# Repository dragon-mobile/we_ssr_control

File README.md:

# we_ssr_control

<br/>

<br/>

The WEMOS Solid State Relay Controller is primarily meant to be
used with an open hardware solid state relay PCBs that is being co-developed
alongside this project as part of my Dragon Mobile GitHub organization to make
useful hardware with associated firmware and software for the tiny home, van
life and maker communities.

## Visual 3D examples

Top view<br/>
<br/>
Bottom view<br/>
<br/>

## Contributing

Contributors are welcome.
Please note that this project has a [Contributor Covenant Code of Conduct].
By participating in this project you agree to abide by its terms.

All intentionally contributed hardware will be considered to be contributed
under the [CERN] license without any additional terms or conditions.

All intentionally contributed code will be considered to be contributed
under a [MIT] license without any additional terms or conditions.
Please include your information in a comment on all code files for the copyright
etc.

All intentionally contributed documentation, CAD files and libraries, footprints,
artwork or non-code text like this README etc. will be considered to be
contributed under the same [CC-BY-SA] license without any additional terms or
conditions.

Pull requests are always welcome. For major changes, please open an issue first
to discuss what you would like to change.
Please make sure to update or add tests as appropriate for all software changes.

## Licenses

<br/>

All hardware is licensed under the

  * [CERN] - CERN-OHL-W-2.0
  
You can find a copy of the CERN Open Hardware License - Weakly-reciprocal v2.0
in the [LICENSE-CERN-OHL-W-2] file and the how-to guide in the
[CERN-HOWTO_GUIDE] file.

All code is licensed under the

  * [MIT] - MIT License

You can find a copy of the license in the [LICENSE-MIT] file.

All documentation like this README is licensed under the Creative Commons
Attribution-ShareAlike 4.0 International License (CC-BY-SA).

All original CAD files and libraries, footprints, and artwork are also licensed
under the
Creative Commons Attribution-ShareAlike 4.0 International License (CC-BY-SA).
You can find a copy of the [CC-BY-SA] license in the [LICENSE-CC-BY-SA] file.

If after reading the above license files, how-tos, and related FAQs on the
linked license sites on how they apply to the project please either open an
issue or contact me (Michael Cummings) via my Github email and I will try
to guided you through my understanding of how it works.

[CC-BY-SA]: http://creativecommons.org/licenses/by-sa/4.0/
[CERN]: https://ohwr.org/project/cernohl/wikis/Documents/CERN-OHL-version-2
[CERN-HOWTO_GUIDE]: docs/cern_ohl_w_v2_howto.pdf
[Contributor Covenant Code of Conduct]: CODE_OF_CONDUCT.md 
[LICENSE-CC-BY-SA]: LICENSE-CC-BY-SA
[LICENSE-CERN-OHL-W-2]: CERN-OHL-W-2
[LICENSE-MIT]: LICENSE-MIT
[MIT]: https://opensource.org/licenses/MIT

<hr>
Copyright &copy; 2022-2023, Michael Cummings<br/>

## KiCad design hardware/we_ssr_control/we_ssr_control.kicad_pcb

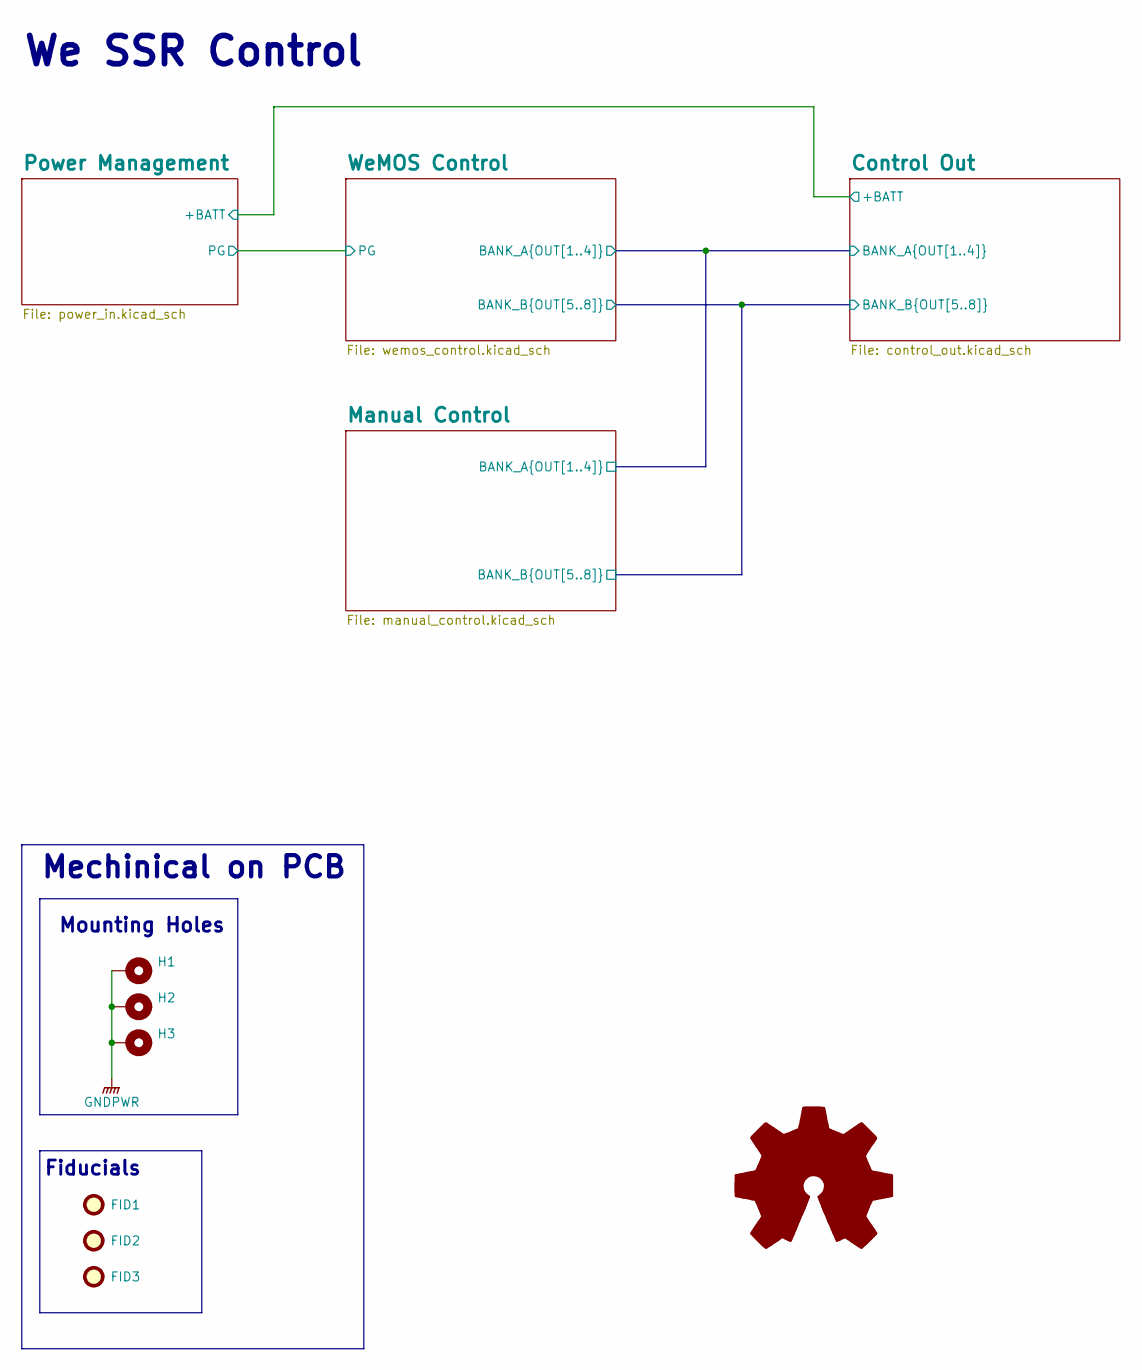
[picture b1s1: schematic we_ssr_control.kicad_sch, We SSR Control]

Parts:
FID1, FID2, FID3: Fiducial; Fiducial_0.5mm_Mask1mm
H1, H2, H3: MountingHole_Pad; MountingHole_3.2mm_M3_Pad_Via

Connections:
GNDPWR: H1.1, H2.1, H3.1; also elsewhere on the board

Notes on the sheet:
Fiducials
We SSR Control
Mechinical on PCB
Mounting Holes

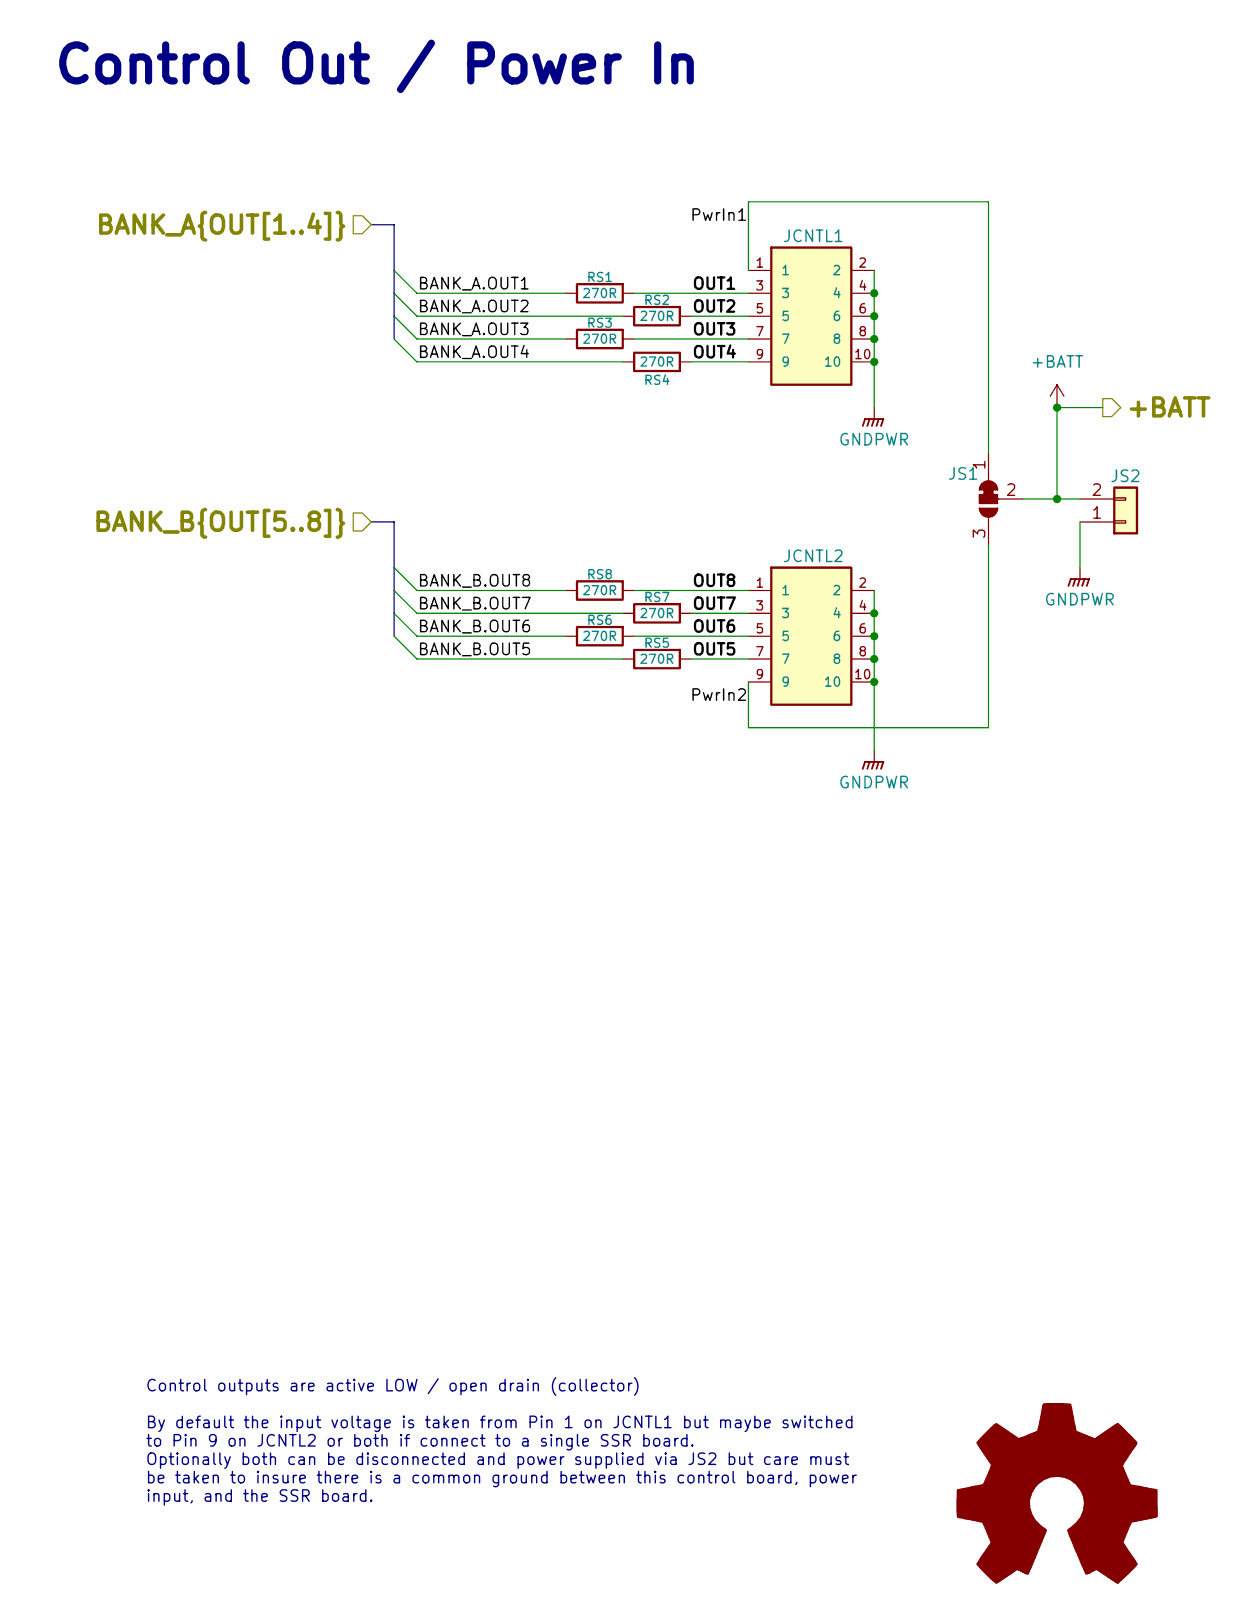
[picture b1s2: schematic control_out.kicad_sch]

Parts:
JCNTL1, JCNTL2: SHF-105-01-L-D-RA; SAMTEC_SHF-105-01-L-D-RA; Mouser Part Number 200-SHF10501LDRATR
JS1: SolderJumper_3_Bridged12; SolderJumper-3_P1.3mm_Bridged12_RoundedPad1.0x1.5mm_NumberL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
JS2: Conn_01x02; PinHeader_1x02_P1.00mm_Vertical
RS1, RS2, RS3, RS4, RS5, RS6, RS7, RS8: 270R; R_0603_1608Metric; Mouser Part Number 755-SDR03EZPJ271

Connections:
+BATT: JS1.2 (C), JS2.2; also elsewhere on the board
/Control Out/BANK_A.OUT1: RS1.1; also elsewhere on the board
/Control Out/BANK_A.OUT2: RS2.1; also elsewhere on the board
/Control Out/BANK_A.OUT3: RS3.1; also elsewhere on the board
/Control Out/BANK_A.OUT4: RS4.1; also elsewhere on the board
/Control Out/BANK_B.OUT5: RS5.1; also elsewhere on the board
/Control Out/BANK_B.OUT6: RS6.1; also elsewhere on the board
/Control Out/BANK_B.OUT7: RS7.1; also elsewhere on the board
/Control Out/BANK_B.OUT8: RS8.1; also elsewhere on the board
/Control Out/OUT1: JCNTL1.3, RS1.2
/Control Out/OUT2: JCNTL1.5, RS2.2
/Control Out/OUT3: JCNTL1.7, RS3.2
/Control Out/OUT4: JCNTL1.9, RS4.2
/Control Out/OUT5: JCNTL2.7, RS5.2
/Control Out/OUT6: JCNTL2.5, RS6.2
/Control Out/OUT7: JCNTL2.3, RS7.2
/Control Out/OUT8: JCNTL2.1, RS8.2
/Control Out/PwrIn1: JCNTL1.1, JS1.1 (A)
/Control Out/PwrIn2: JCNTL2.9, JS1.3 (B)
GNDPWR: JCNTL1.2, JCNTL1.4, JCNTL1.6, JCNTL1.8, JCNTL1.10, JCNTL2.2, JCNTL2.4, JCNTL2.6, JCNTL2.8, JCNTL2.10, JS2.1; also elsewhere on the board

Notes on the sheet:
Control Out / Power In
Control outputs are active LOW / open drain (collector) By default the input voltage is taken from Pin 1 on JCNTL1 but maybe switched to Pin 9 on JCNTL2 or both if connect to a single SSR board. Optionally both can be disconnected and power supplied via JS2 but care must be taken to insure there is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

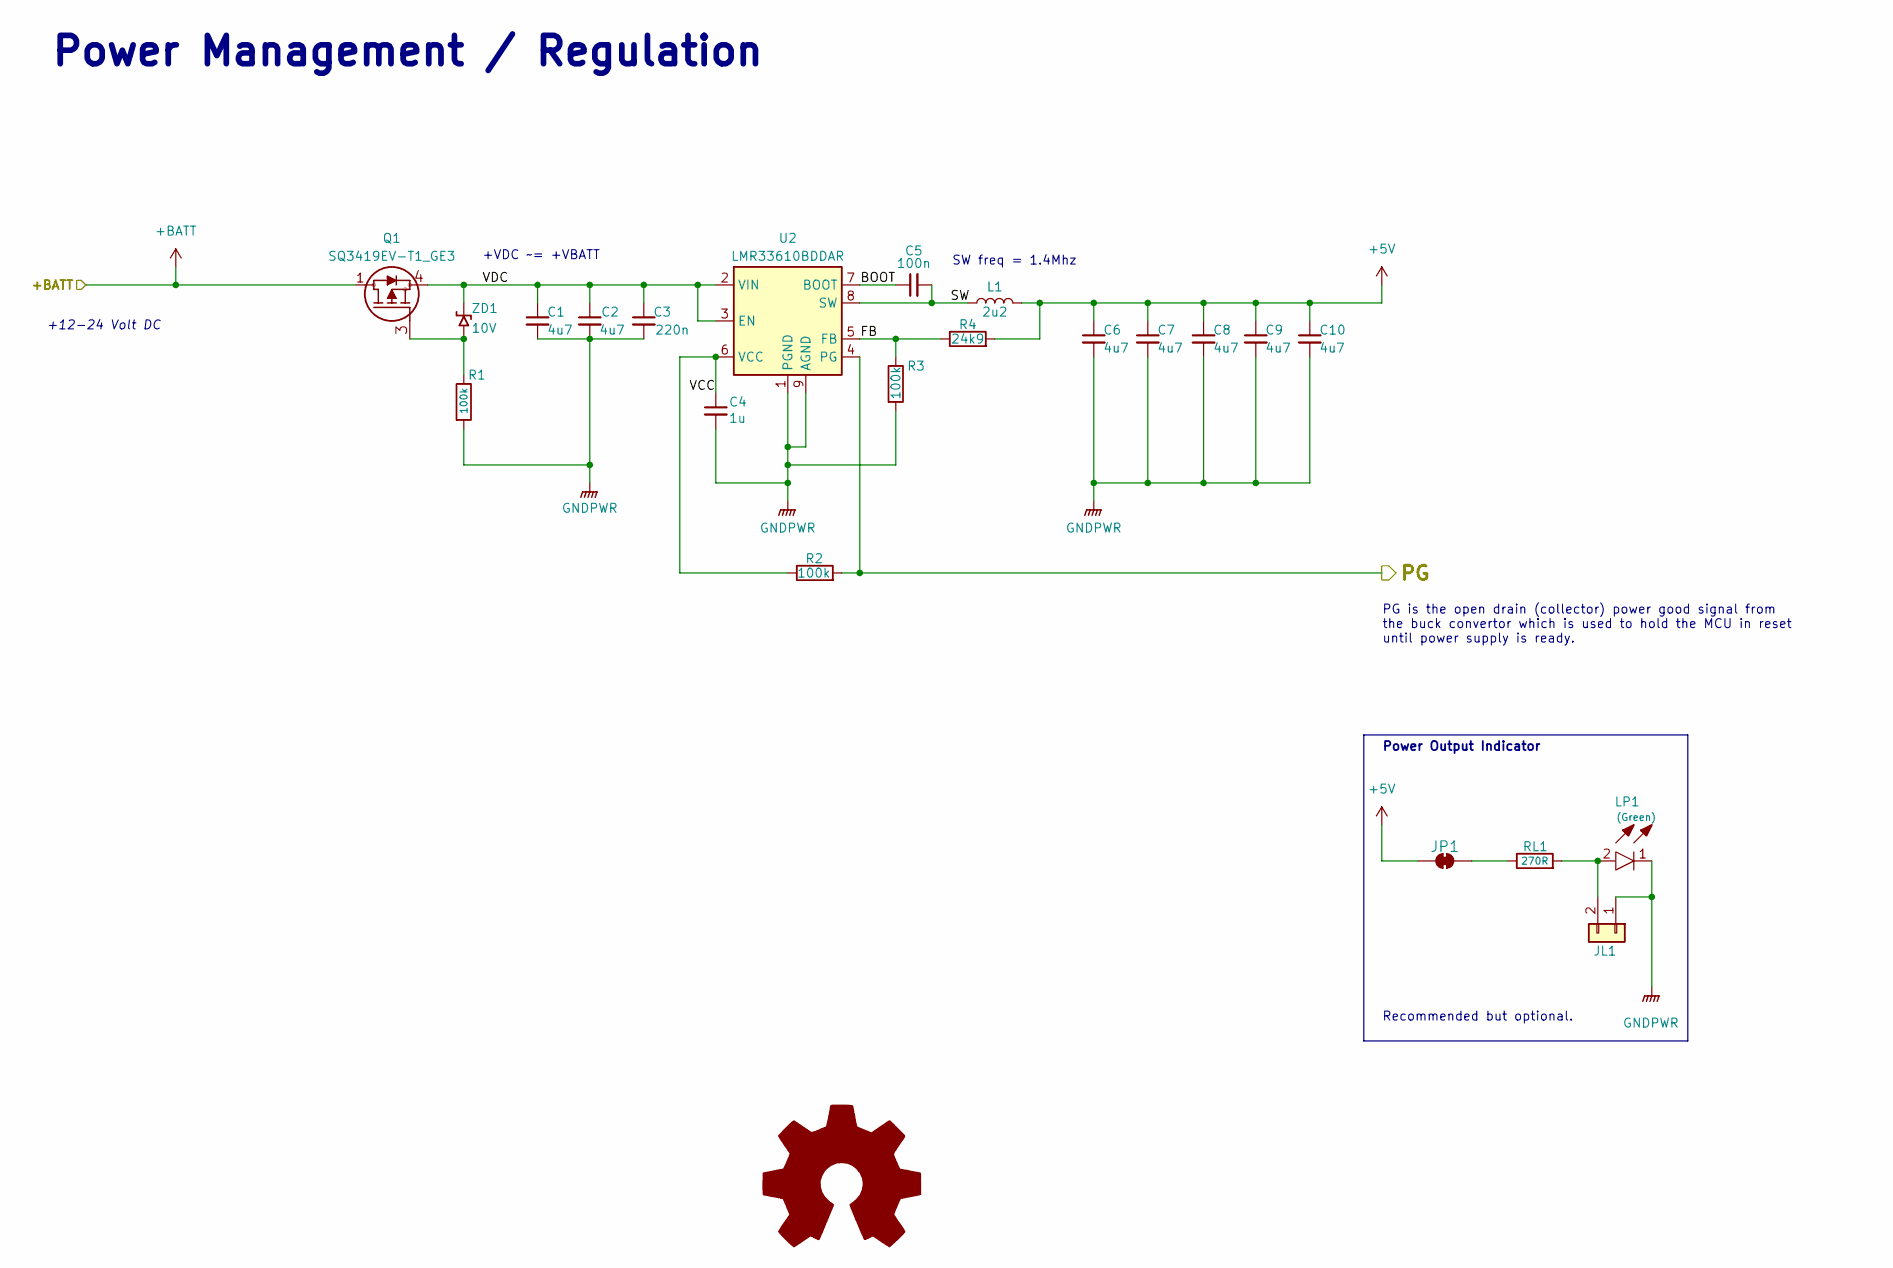
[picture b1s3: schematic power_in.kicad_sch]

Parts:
C1, C2, C6, C7, C8, C9, C10: 4u7; C_0805_2012Metric; Mouser Part Number 810-CGA4J1X7R1H475K1
C3: 220n; C_0603_1608Metric; Mouser Part Number 810-CGA3E3X7R1H224K
C4: 1u; C_0603_1608Metric; Mouser Part Number 810-CGA3E3X5R1H105K
C5: 100n; C_0603_1608Metric; Mouser Part Number 810-CGA3E2X7R1H104K
JL1: Conn_01x02; PinHeader_1x02_P1.00mm_Vertical
JP1: SolderJumper_2_Bridged; SolderJumper-2_P1.3mm_Bridged_RoundedPad1.0x1.5mm
L1: 2u2; L_1008_2520Metric; Mouser Part Number 810-TFM252012ALVA2R2
LP1: LTST-C190KGKT; LEDC1608X80N; Mouser Part Number 859-LTST-C190KGKT
Q1: SQ3419EV-T1_GE3; SOT95P284X110-6N; Mouser Part Number 78-SQ3419EV-T1_GE3
R1, R2, R3: 100k; R_0603_1608Metric; Mouser Part Number 667-ERJ-PA3F1003V
R4: 24k9; R_0603_1608Metric; Mouser Part Number 667-ERJ-PA3F2492V
RL1: 270R; R_0603_1608Metric; Mouser Part Number 755-SDR03EZPJ271
U2: LMR33610BDDAR; Texas_HSOP-8-1EP_3.9x4.9mm_P1.27mm_ThermalVias; Mouser Part Number 595-LMR33610BDDAR
ZD1: 10V; D_0805_2012Metric; Mouser Part Number 821-BZY55B10RBG

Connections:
+5V: C6.1, C7.1, C8.1, C9.1, C10.1, JP1.1 (A), L1.2, R4.2; also elsewhere on the board
+BATT: Q1.1 (D), Q1.2 (D), Q1.5 (D), Q1.6 (D); also elsewhere on the board
/Power Management/BOOT: C5.1, U2.7 (BOOT)
/Power Management/FB: R3.1, R4.1, U2.5 (FB)
/Power Management/PG: R2.2, U2.4 (PG); also elsewhere on the board
/Power Management/SW: C5.2, L1.1, U2.8 (SW)
/Power Management/VCC: C4.1, R2.1, U2.6 (VCC)
/Power Management/VDC: C1.1, C2.1, C3.1, Q1.4 (S), U2.2 (VIN), U2.3 (EN), ZD1.1
GNDPWR: C1.2, C2.2, C3.2, C4.2, C6.2, C7.2, C8.2, C9.2, C10.2, JL1.1, LP1.1, R1.2, R3.2, U2.1 (PGND), U2.9 (AGND); also elsewhere on the board
unnamed: JL1.2, LP1.2, RL1.2
unnamed: JP1.2 (B), RL1.1
unnamed: Q1.3 (G), R1.1, ZD1.2

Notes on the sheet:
+12-24 Volt DC
PG is the open drain (collector) power good signal from the buck convertor which is used to hold the MCU in reset until power supply is ready.
Recommended but optional.
SW freq = 1.4Mhz
Power Management / Regulation
Power Output Indicator
+VDC ~= +VBATT

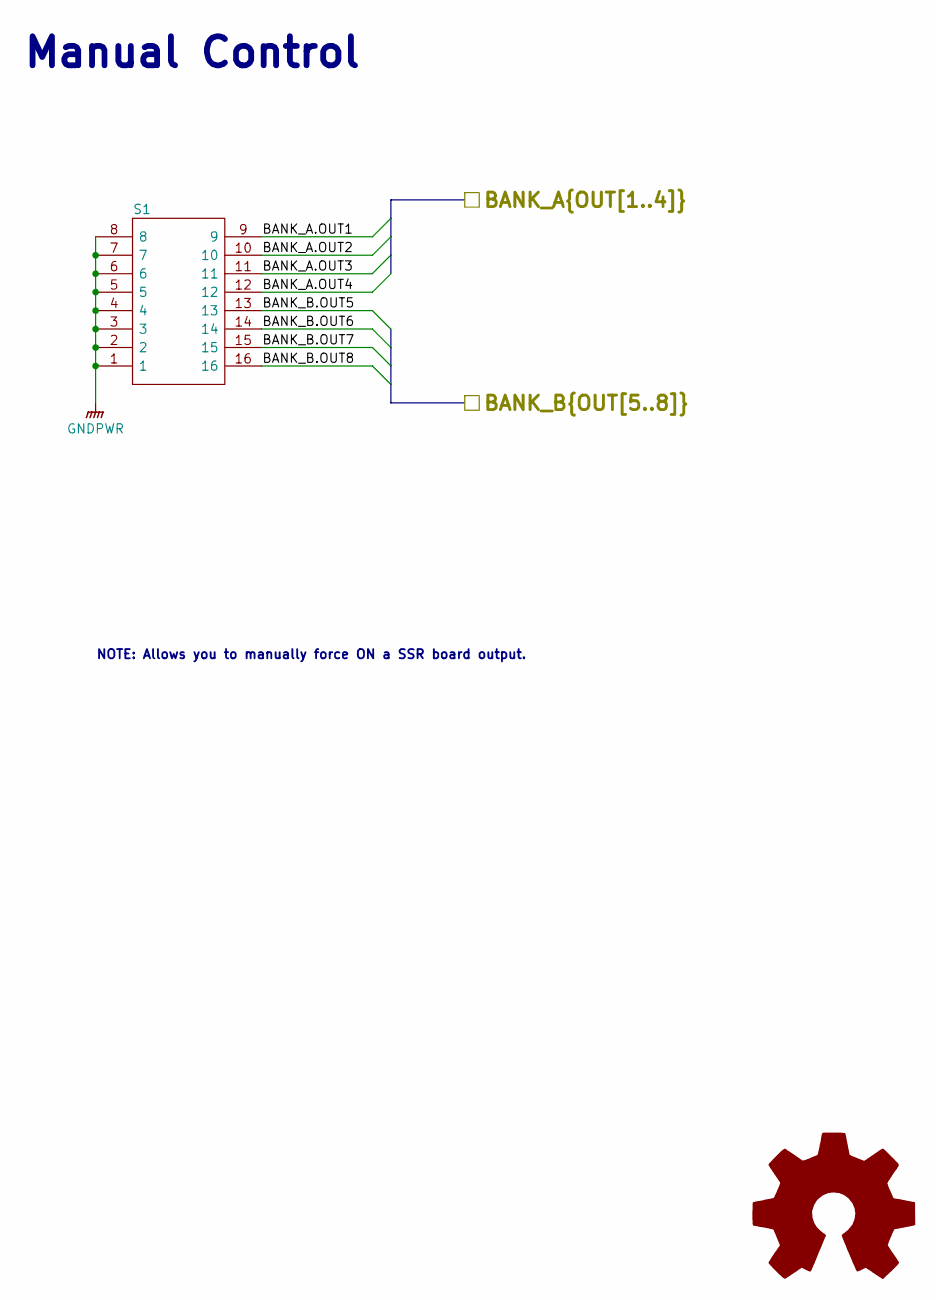
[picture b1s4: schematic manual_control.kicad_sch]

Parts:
S1: 193-8MS; 1938MS; Mouser Part Number 774-1938MS

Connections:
/Control Out/BANK_A.OUT1: S1.9; also elsewhere on the board
/Control Out/BANK_A.OUT2: S1.10; also elsewhere on the board
/Control Out/BANK_A.OUT3: S1.11; also elsewhere on the board
/Control Out/BANK_A.OUT4: S1.12; also elsewhere on the board
/Control Out/BANK_B.OUT5: S1.13; also elsewhere on the board
/Control Out/BANK_B.OUT6: S1.14; also elsewhere on the board
/Control Out/BANK_B.OUT7: S1.15; also elsewhere on the board
/Control Out/BANK_B.OUT8: S1.16; also elsewhere on the board
GNDPWR: S1.1, S1.2, S1.3, S1.4, S1.5, S1.6, S1.7, S1.8; also elsewhere on the board

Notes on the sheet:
Manual Control
NOTE: Allows you to manually force ON a SSR board output.

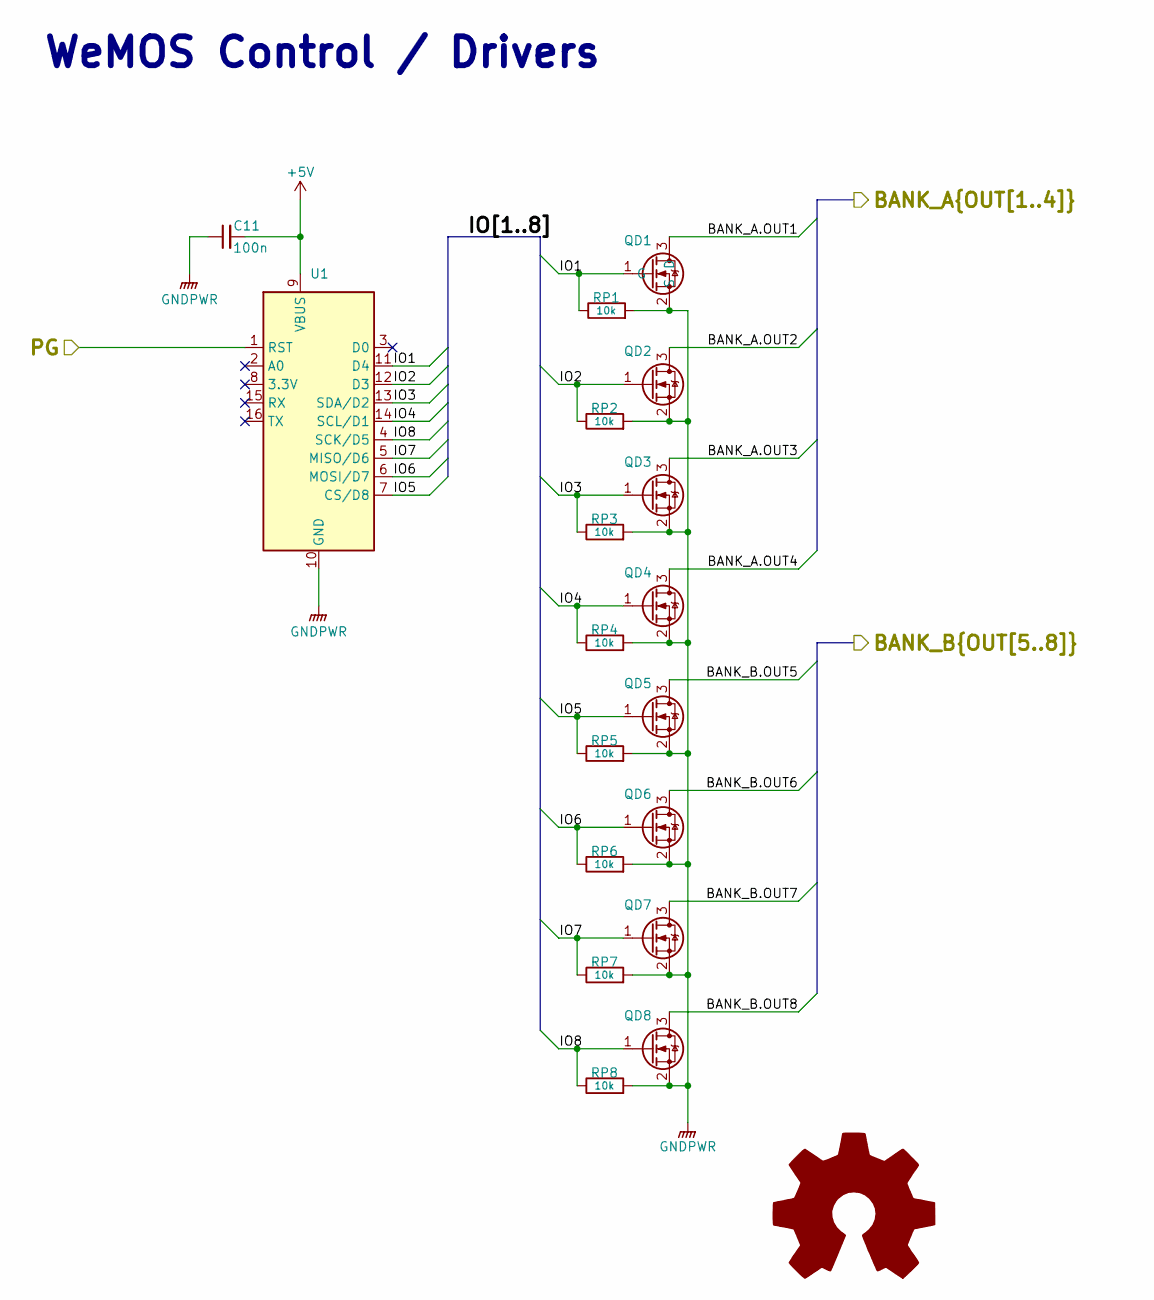
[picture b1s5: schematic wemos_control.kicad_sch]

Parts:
C11: 100n; C_0603_1608Metric; Mouser Part Number 810-CGA3E2X7R1H104K
QD1, QD2, QD3, QD4, QD5, QD6, QD7, QD8: 2N7002K; 2V7002KT1G; Mouser Part Number 863-2V7002KT1G
RP1, RP2, RP3, RP4, RP5, RP6, RP7, RP8: 10k; R_0603_1608Metric; Mouser Part Number 755-SDR03EZPJ103
U1: WeMos_D1_mini; WEMOS_D1_mini_light

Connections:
+5V: C11.2, U1.9 (VBUS); also elsewhere on the board
/Control Out/BANK_A.OUT1: QD1.3 (D); also elsewhere on the board
/Control Out/BANK_A.OUT2: QD2.3 (D); also elsewhere on the board
/Control Out/BANK_A.OUT3: QD3.3 (D); also elsewhere on the board
/Control Out/BANK_A.OUT4: QD4.3 (D); also elsewhere on the board
/Control Out/BANK_B.OUT5: QD5.3 (D); also elsewhere on the board
/Control Out/BANK_B.OUT6: QD6.3 (D); also elsewhere on the board
/Control Out/BANK_B.OUT7: QD7.3 (D); also elsewhere on the board
/Control Out/BANK_B.OUT8: QD8.3 (D); also elsewhere on the board
/Power Management/PG: U1.1 (RST); also elsewhere on the board
/WeMOS Control/IO1: QD1.1 (G), RP1.1, U1.11 (D4)
/WeMOS Control/IO2: QD2.1 (G), RP2.1, U1.12 (D3)
/WeMOS Control/IO3: QD3.1 (G), RP3.1, U1.13 (SDA/D2)
/WeMOS Control/IO4: QD4.1 (G), RP4.1, U1.14 (SCL/D1)
/WeMOS Control/IO5: QD5.1 (G), RP5.1, U1.7 (CS/D8)
/WeMOS Control/IO6: QD6.1 (G), RP6.1, U1.6 (MOSI/D7)
/WeMOS Control/IO7: QD7.1 (G), RP7.1, U1.5 (MISO/D6)
/WeMOS Control/IO8: QD8.1 (G), RP8.1, U1.4 (SCK/D5)
GNDPWR: C11.1, QD1.2 (S), QD2.2 (S), QD3.2 (S), QD4.2 (S), QD5.2 (S), QD6.2 (S), QD7.2 (S), QD8.2 (S), RP1.2, RP2.2, RP3.2, RP4.2, RP5.2, RP6.2, RP7.2, RP8.2, U1.10 (GND); also elsewhere on the board

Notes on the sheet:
WeMOS Control / Drivers

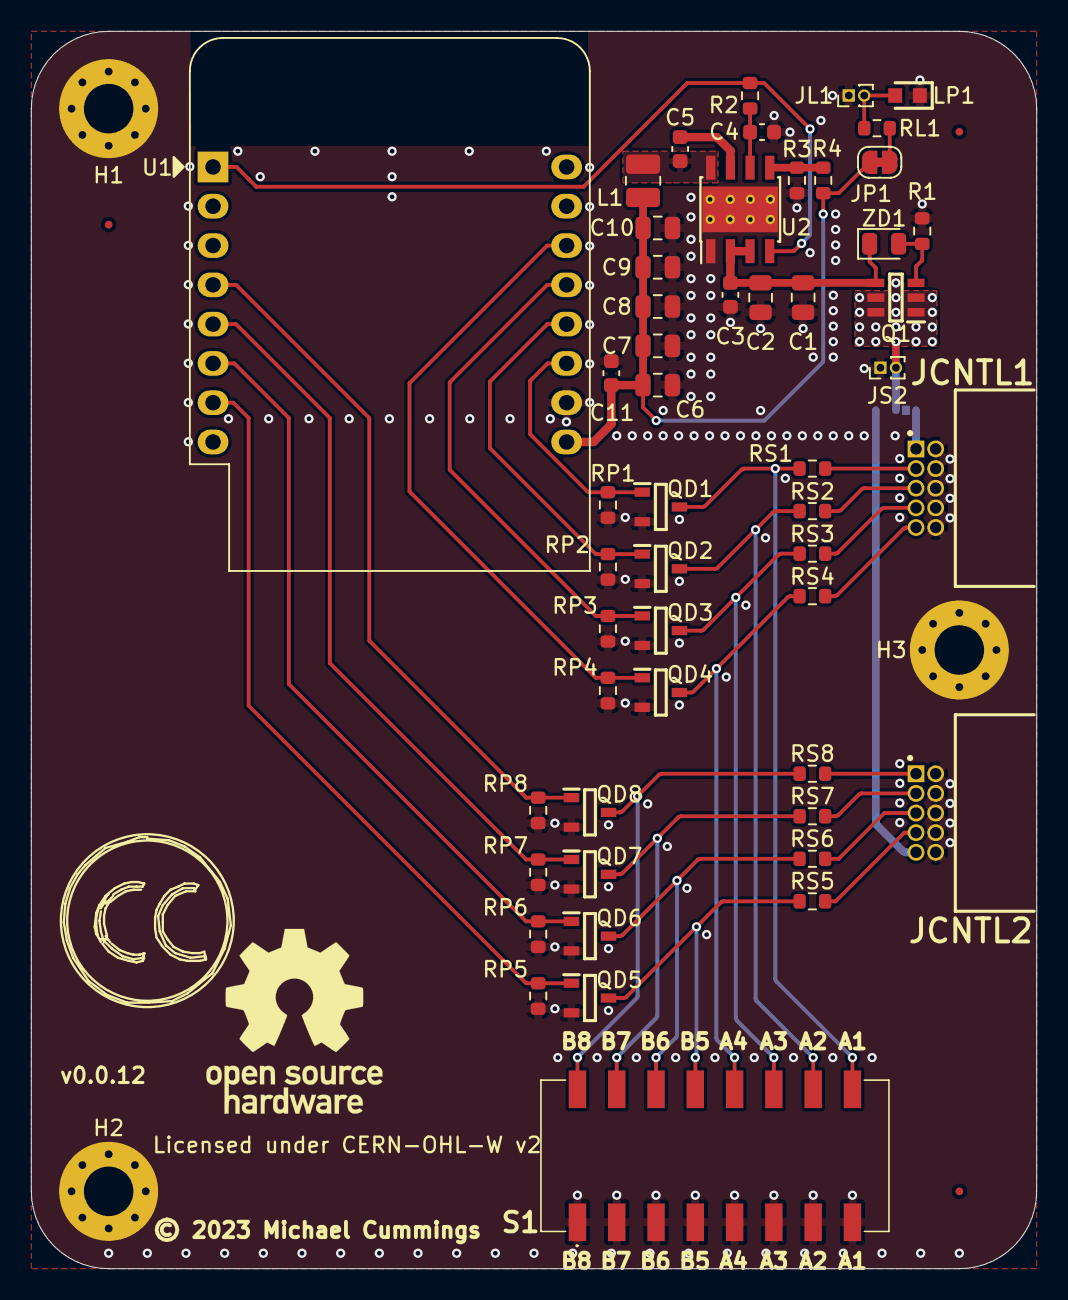
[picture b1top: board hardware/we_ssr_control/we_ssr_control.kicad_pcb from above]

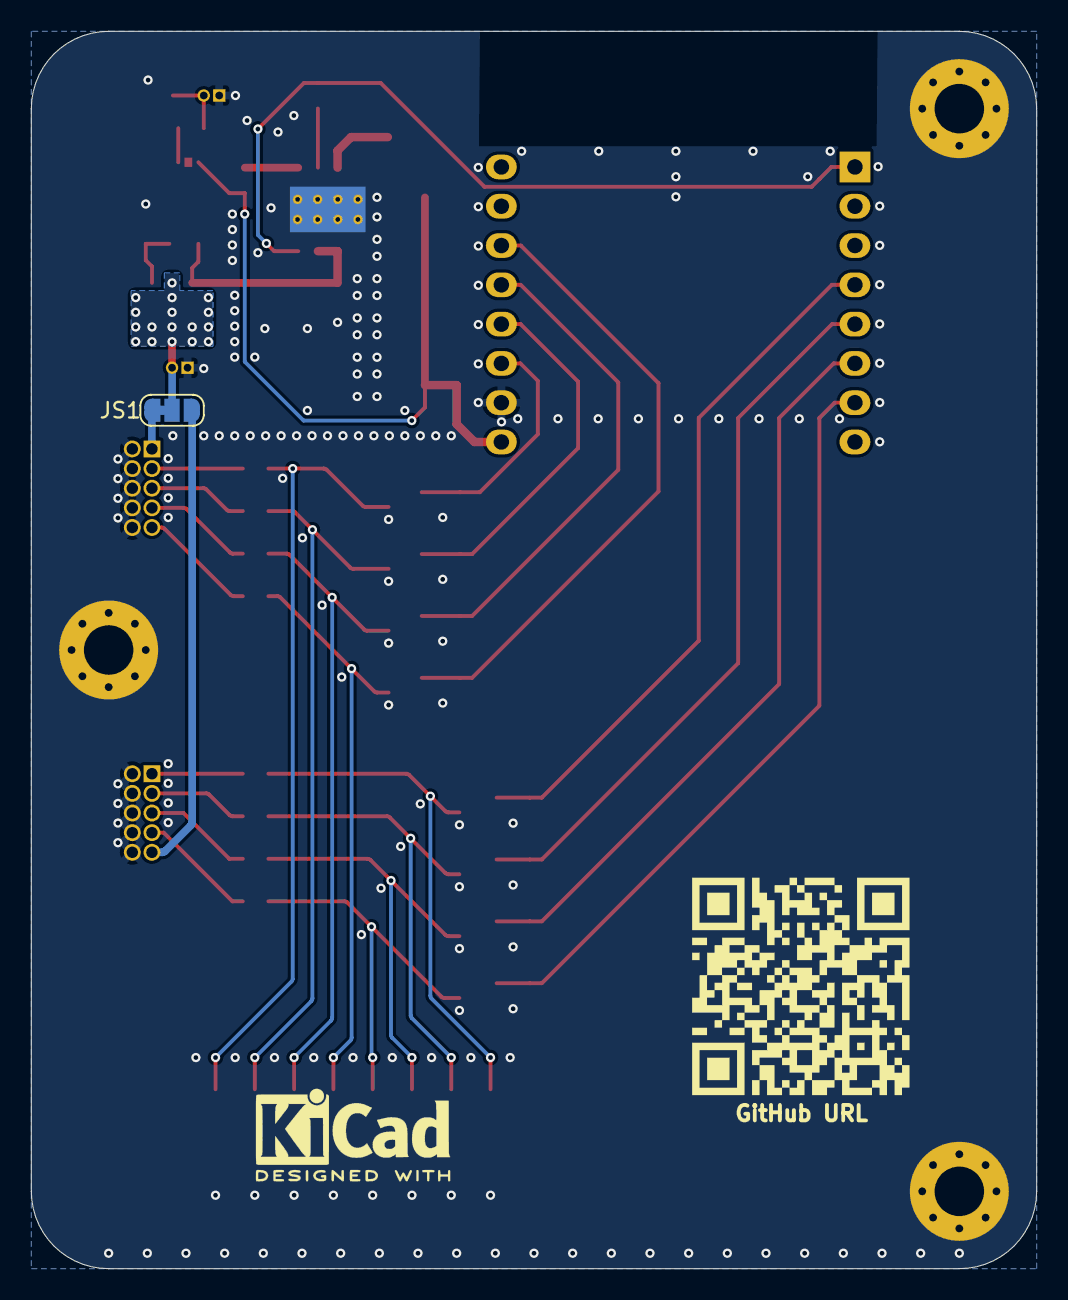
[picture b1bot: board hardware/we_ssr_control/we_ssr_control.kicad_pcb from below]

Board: 2 copper layers, 65.0 x 80.0 mm, 63 parts (3 on the bottom side), 38 nets.

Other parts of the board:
JCNTL1_Label: JCNTL1_Label
JCNTL2_Label: JCNTL2_Label
QRCode1: GitHub URL; LOGO
REF_KiCAD: KiCad-Logo2_5mm_SilkScreen

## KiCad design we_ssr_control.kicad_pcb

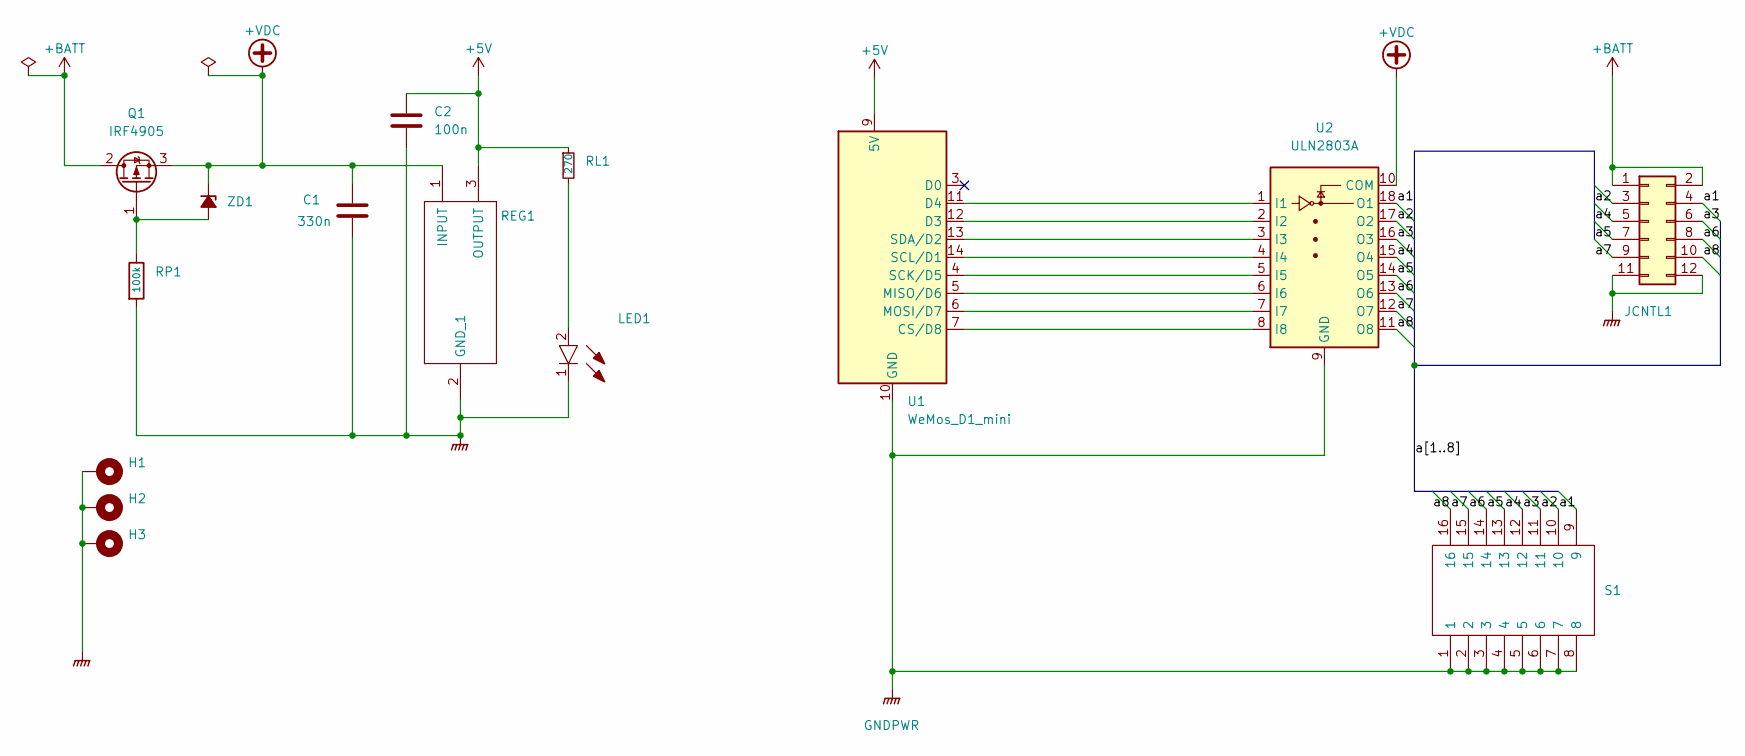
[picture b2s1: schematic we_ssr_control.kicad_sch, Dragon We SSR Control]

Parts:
C1: 330n; C_0805_2012Metric; Mfr. #: C0805C334K5RACAUTO
C2: 100n; C_0805_2012Metric; Mfr. #: C0805X104K5RAC3316
H1, H2, H3: MountingHole_Pad; MountingHole_3.2mm_M3_Pad_Via
JCNTL1: Conn_02x06_Odd_Even; IDC-Header_2x06_P2.54mm_Horizontal
LED1: LTST-C190KGKT; LEDC1608X80N; Mouser Part Number 859-LTST-C190KGKT
Q1: IRF4905; TO-220-3_Vertical
REG1: LM7805; SOT-223; Mouser Part Number 595-LM7805MPX/NOPB
RL1: 270; R_0603_1608Metric; Mfr. #: SDR03EZPJ271; Mouser #: 755-SDR03EZPJ271
RP1: 100k; R_0805_2012Metric; Mfr. #: SDR03EZPF1003
S1: 193-8MS; 1938MS; Mouser Part Number 774-1938MS
U1: WeMos_D1_mini; WEMOS_D1_mini_light
U2: ULN2803A; DIP-18_W7.62mm
ZD1: +10v Zener Diode; D_SMF; Mouser # 78-BZD27C10P-M3-08

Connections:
+5V: C2.1, REG1.3 (OUTPUT), RL1.1, U1.9 (5V)
+BATT: JCNTL1.1, JCNTL1.2, Q1.2 (D)
+VDC: C1.1, Q1.3 (S), REG1.1 (INPUT), U2.10 (COM), ZD1.1 (K)
/a1: JCNTL1.4, S1.9, U2.18 (O1)
/a2: JCNTL1.3, S1.10, U2.17 (O2)
/a3: JCNTL1.6, S1.11, U2.16 (O3)
/a4: JCNTL1.5, S1.12, U2.15 (O4)
/a5: JCNTL1.7, S1.13, U2.14 (O5)
/a6: JCNTL1.8, S1.14, U2.13 (O6)
/a7: JCNTL1.9, S1.15, U2.12 (O7)
/a8: JCNTL1.10, S1.16, U2.11 (O8)
GNDPWR: C1.2, C2.2, H1.1, H2.1, H3.1, JCNTL1.11, JCNTL1.12, LED1.1, REG1.2 (GND_1), REG1.4 (GND_2), RP1.2, S1.1, S1.2, S1.3, S1.4, S1.5, S1.6, S1.7, S1.8, U1.10 (GND), U2.9 (GND)
unnamed: LED1.2, RL1.2
unnamed: Q1.1 (G), RP1.1, ZD1.2 (A)
unnamed: U1.4 (SCK/D5), U2.5 (I5)
unnamed: U1.5 (MISO/D6), U2.6 (I6)
unnamed: U1.6 (MOSI/D7), U2.7 (I7)
unnamed: U1.7 (CS/D8), U2.8 (I8)
unnamed: U1.11 (D4), U2.1 (I1)
unnamed: U1.12 (D3), U2.2 (I2)
unnamed: U1.13 (SDA/D2), U2.3 (I3)
unnamed: U1.14 (SCL/D1), U2.4 (I4)

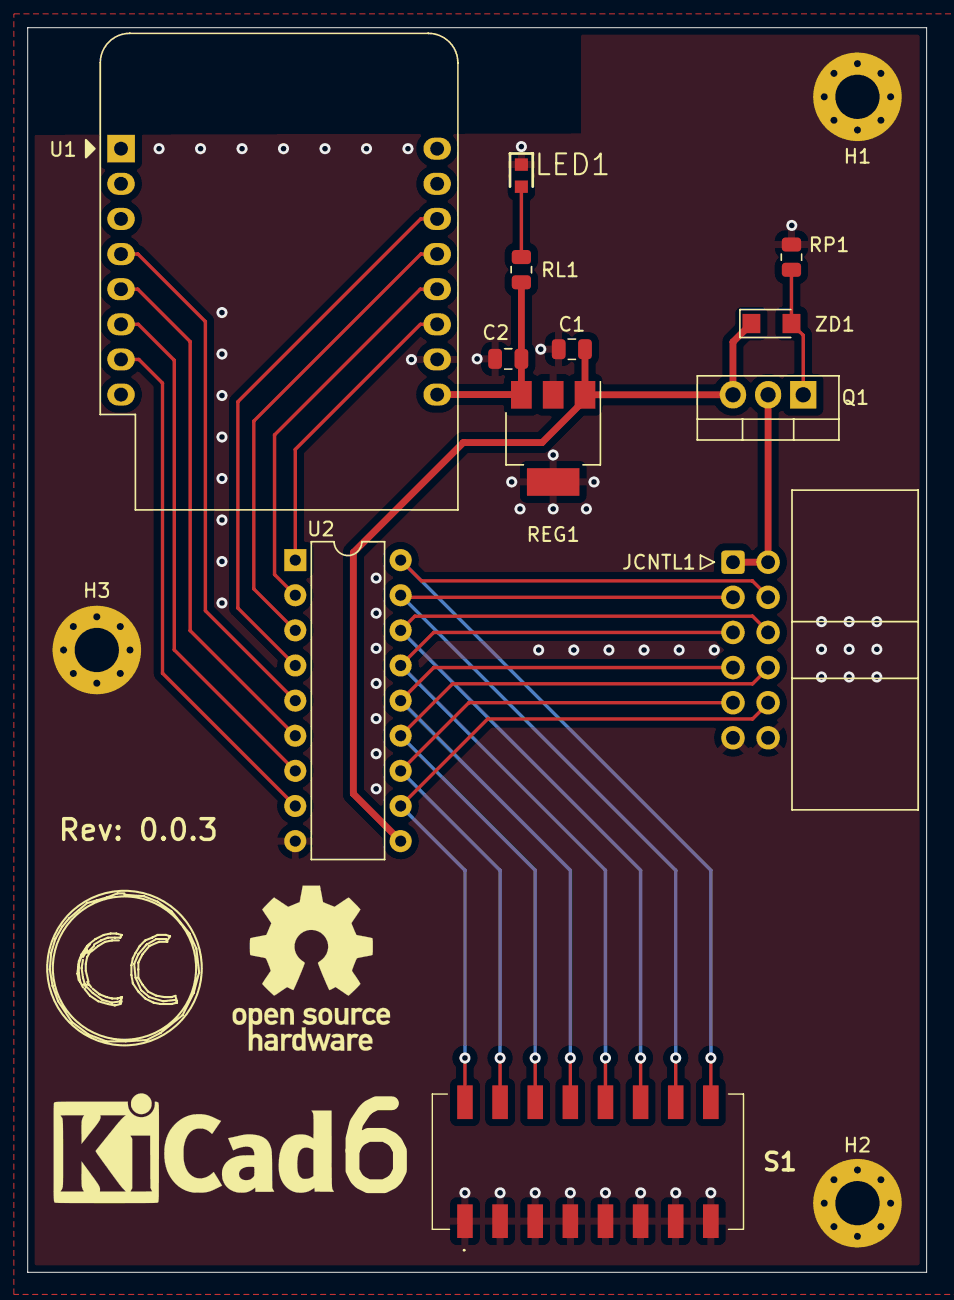
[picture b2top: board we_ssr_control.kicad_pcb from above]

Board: 2 copper layers, 65.0 x 90.0 mm, 15 parts (0 on the bottom side), 22 nets.

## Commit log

2022-07-18 sync local with remote
2022-08-11 Major re-orginization of project
2022-12-09 WIP control connector changes
2023-01-04 WIP for updated layout
2023-01-10 Add PCB images to docs/
2023-01-10 Add first draft production files
2023-01-10 Updated README and added MountingTemplate in docs/
2023-01-10 Minor updates for v0.0.9
2023-01-29 Changed schematic to hierarchical style with mutliple sheets
2023-01-29 Updated metadata to v0.0.10
2023-01-29 Misc updates to Scheme files.
2023-01-29 Cleanup PCB traces.
2023-02-03 Corrected footprint of RZ1 from 0805 to 0603
2023-02-03 Cleanup of old footprints,3dmodels, and symbols
2023-02-03 Merged all symbol, 3dmodel, and footprint changes
2023-02-03 Updated metadata
2023-02-08 Power supply changes plus misc.
2023-02-13 Pre KiCad 7.0.0 WIP
2023-02-13 Added share_components submodule
2023-02-13 Updated to KiCAD 7 and some footprint updates
2023-03-16 Commit before removing git submodules

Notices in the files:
README.md:
https://img.shields.io/static/v1?label=license&message=CERN-OHL-W-2.0%20%2F%20MIT%20%2F%20CC-BY-SA-4.0&color=orange
CC BY-SA 4.0
hardware/we_ssr_control/control_out.kicad_sch:
creativecommons.org/licenses/by/4.0
License: CC By 4.0
Hardware License: CERN-OHL-W
hardware/we_ssr_control/we_ssr_control.kicad_pcb:
© 2023 Michael Cummings
Licensed under CERN-OHL-W v2
we_ssr_control.kicad_pcb:
© 2022 Michael Cummings
